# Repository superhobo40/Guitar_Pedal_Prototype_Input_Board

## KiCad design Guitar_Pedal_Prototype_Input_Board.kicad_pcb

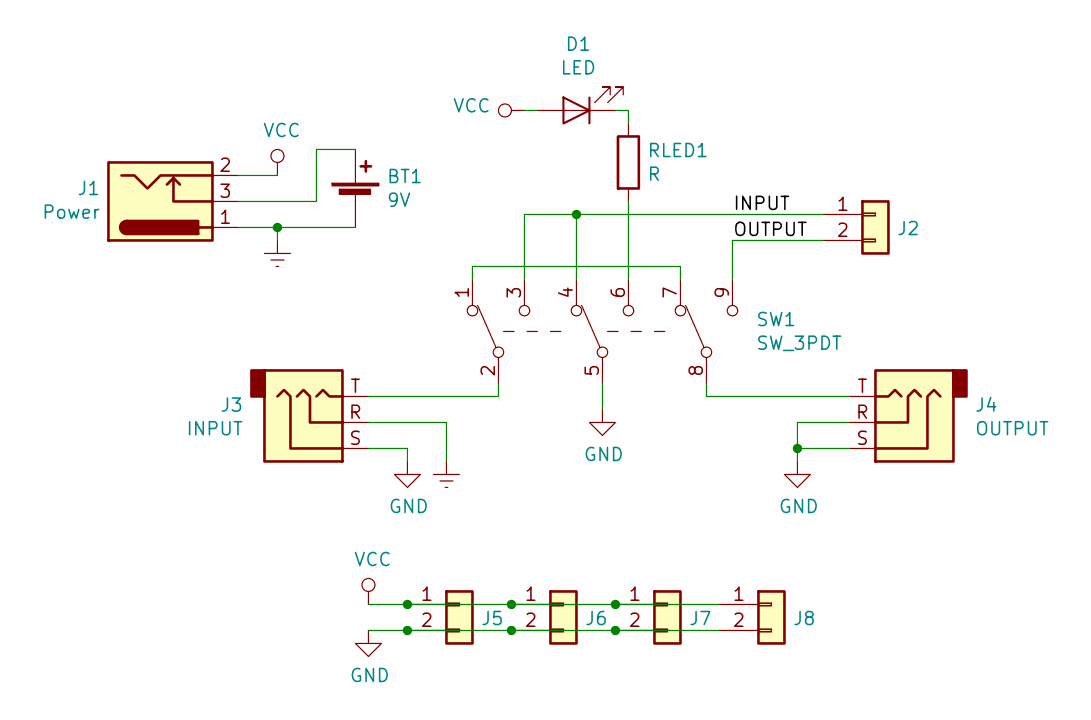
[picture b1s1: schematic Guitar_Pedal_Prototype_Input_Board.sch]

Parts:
BT1: 9V; 1X02
D1: LED; LED_D5.0mm
J1: Power; BARREL_JACK
J2, J5, J6, J7, J8: Conn_01x02; 1X02
J3: INPUT; AUDIO_JACK_0.25%5c%22_TRS_PTH_RA
J4: OUTPUT; AUDIO_JACK_0.25%5c%22_TRS_PTH_RA
RLED1: R; R_Axial_DIN0207_L6.3mm_D2.5mm_P7.62mm_Horizontal
SW1: SW_3PDT; STOMP_SWITCH_3PDT

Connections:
/INPUT: J2.1, SW1.3 (C), SW1.4 (A)
/OUTPUT: J2.2, SW1.9 (C)
Earth: BT1.2 (-), J1.1, J3.R
GND: J3.S, J4.R, J4.S, J5.2, J6.2, J7.2, J8.2, SW1.5 (B)
unnamed: BT1.1 (+), J1.3
unnamed: D1.1 (K), RLED1.1
unnamed: J3.T, SW1.2 (B)
unnamed: J4.T, SW1.8 (B)
unnamed: RLED1.2, SW1.6 (C)
unnamed: SW1.1 (A), SW1.7 (A)
VCC: D1.2 (A), J1.2, J5.1, J6.1, J7.1, J8.1

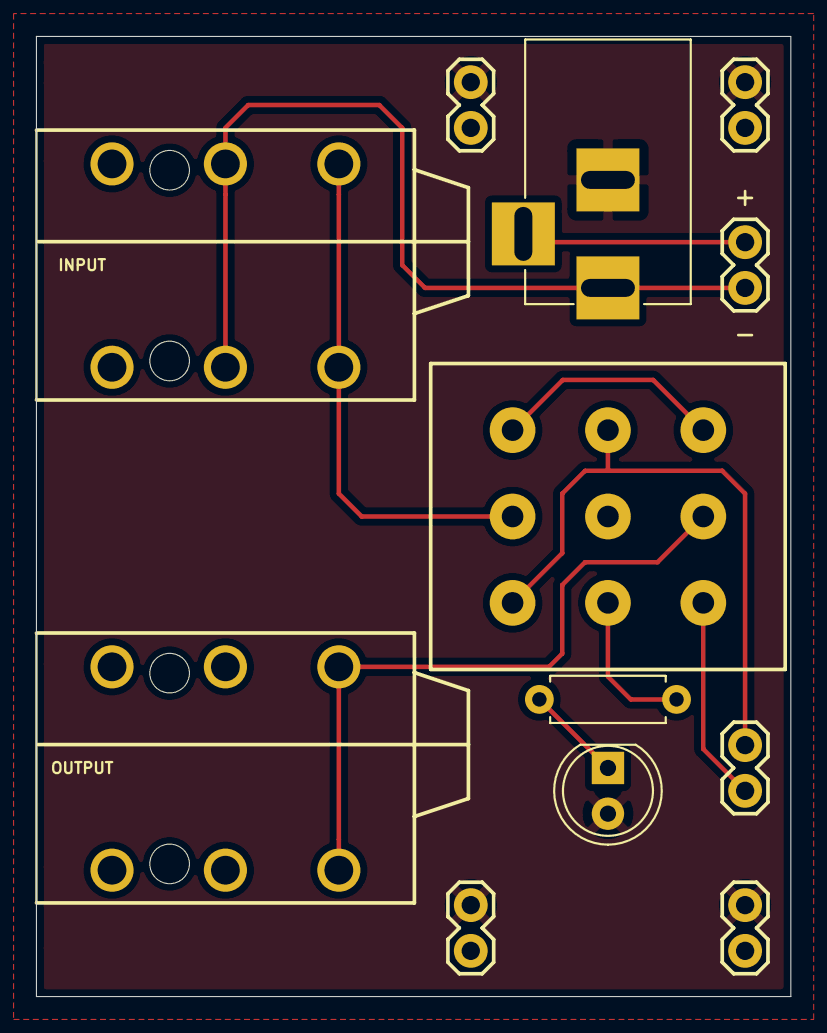
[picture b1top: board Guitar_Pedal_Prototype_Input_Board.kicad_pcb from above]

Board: 2 copper layers, 41.9 x 53.3 mm, 12 parts (0 on the bottom side), 11 nets.

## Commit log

2020-02-25 Actually added the files.
